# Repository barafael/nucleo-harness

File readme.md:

# Nucleo Harness

This circuit board is a harness for a nucleo board. It allows to embed a nucleo into a reproducible environment (less jumper wires).
2x16 pins can be connected to a saleae 16 protocol analyzer or any other 2x8 connector.
The mapping of pins which are connected to the 2x8 connectors can be made with jumper wires or with small addon PCBs.
Additionally, labeled pin header/sockets expose the regular nucleo64 pins.

TODO: duplicate programming connectors, allow for optional smd pullups

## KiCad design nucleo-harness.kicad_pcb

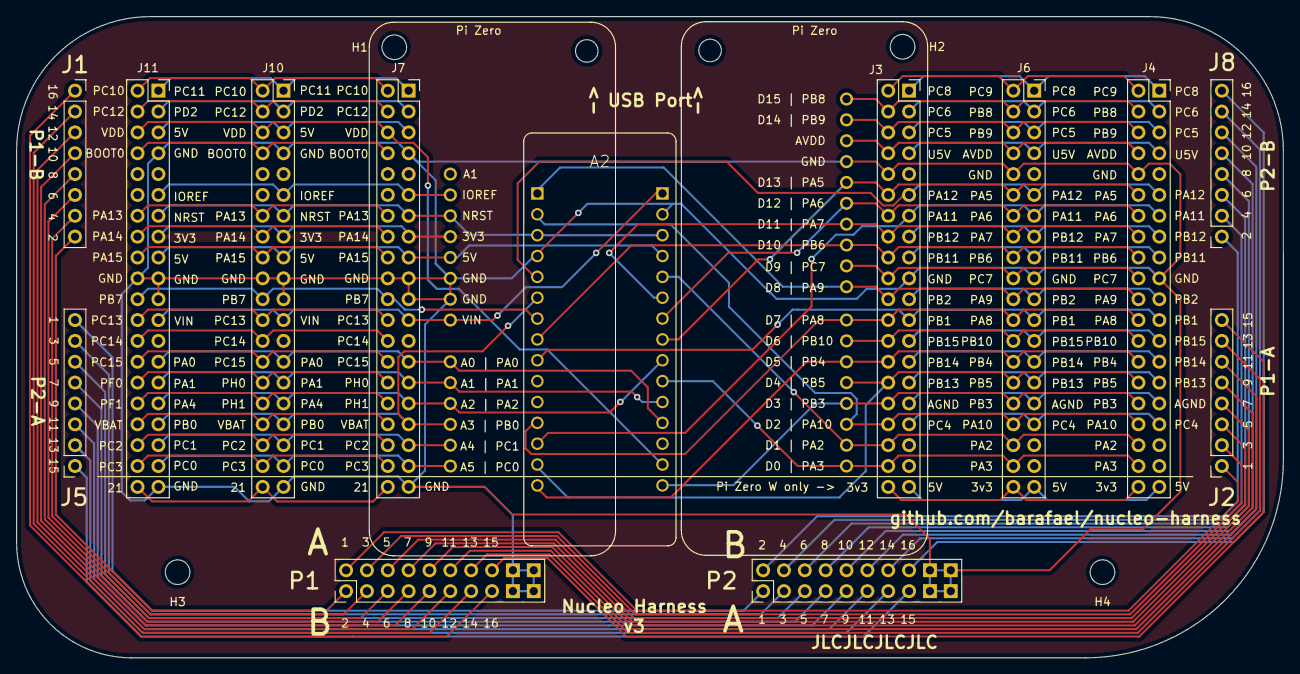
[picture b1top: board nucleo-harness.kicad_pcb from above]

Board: 2 copper layers, 154.3 x 78.1 mm, 18 parts (1 on the bottom side), 99 nets.

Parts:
A1: Arduino_UNO_R3
A2: NUCLEO-32; MODULE_NUCLEO-F303K8
H1, H2, H3, H4: MountingHole; MountingHole_3mm
J1, J2, J5, J8: Conn_01x08_Female; PinSocket_1x08_P2.54mm_Vertical
J3, J4, J6, J7, J10, J11: Conn_02x20_Odd_Even; PinSocket_2x20_P2.54mm_Vertical
P1, P2: Conn_02x10_Odd_Even; PinHeader_2x10_P2.54mm_Vertical

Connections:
3V3: A1.4, J7.15, J10.15, J11.15
5V: A1.5, A2.4.4, J7.17, J10.17, J11.17
AGND: J3.31, J4.31, J6.31
AVDD: A1.30, J3.8, J4.8, J6.8
BOOT0: J7.8, J10.8, J11.8
E5V: J7.5, J10.5, J11.5
GND: A1.6, A1.7, A1.29, A2.3.4, A2.4.2, J3.10, J3.19, J4.10, J4.19, J6.10, J6.19, J7.7, J7.19, J7.20, J7.21, J7.39, J10.7, J10.19, J10.20, J10.21, J10.39, J11.7, J11.19, J11.20, J11.21, J11.39, P1.17, P1.18, P1.19, P1.20, P2.17, P2.18, P2.19, P2.20
GPIO21: J7.40, J10.40, J11.40
IOREF: A1.2, J7.11, J10.11, J11.11
NRST: A1.3, A2.3.3, A2.4.3, J7.13, J10.13, J11.13
unnamed: J1.1, P1.15
unnamed: J1.2, P1.13
unnamed: J1.3, P1.11
unnamed: J1.4, P1.9
unnamed: J1.5, P1.7
unnamed: J1.6, P1.5
unnamed: J1.7, P1.3
unnamed: J1.8, P1.1
unnamed: J2.1, P1.2
unnamed: J2.2, P1.4
unnamed: J2.3, P1.6
unnamed: J2.4, P1.8
unnamed: J2.5, P1.10
unnamed: J2.6, P1.12
unnamed: J2.7, P1.14
unnamed: J2.8, P1.16
unnamed: J5.1, P2.15
unnamed: J5.2, P2.13
unnamed: J5.3, P2.11
unnamed: J5.4, P2.9
unnamed: J5.5, P2.7
unnamed: J5.6, P2.5
unnamed: J5.7, P2.3
unnamed: J5.8, P2.1
unnamed: J8.1, P2.2
unnamed: J8.2, P2.4
unnamed: J8.3, P2.6
unnamed: J8.4, P2.8
unnamed: J8.5, P2.10
unnamed: J8.6, P2.12
unnamed: J8.7, P2.14
unnamed: J8.8, P2.16
PA0: A1.9, A2.4.12, J7.27, J10.27, J11.27
PA1: A1.10, A2.4.11, J7.29, J10.29, J11.29
PA2: A1.16, A2.4.5, J3.36, J4.36, J6.36
PA3: A1.15, A2.4.10, J3.38, J4.38, J6.38
PA4: A1.11, A2.4.9, J7.31, J10.31, J11.31
PA5: A1.28, A2.4.8, J3.12, J4.12, J6.12
PA6: A1.27, A2.4.7, J3.14, J4.14, J6.14
PA7: A1.26, A2.4.6, J3.16, J4.16, J6.16
PA8: A1.22, A2.3.12, J3.24, J4.24, J6.24
PA9: A1.23, A2.3.1, J3.22, J4.22, J6.22
PA10: A1.17, A2.3.2, J3.34, J4.34, J6.34
PA11: A2.3.13, J3.13, J4.13, J6.13
PA12: A2.3.5, J3.11, J4.11, J6.11
PA13: J7.14, J10.14, J11.14
PA14: J7.16, J10.16, J11.16
PA15: J7.18, J10.18, J11.18
PB0: A1.12, A2.3.6, J7.33, J10.33, J11.33
PB1: A2.3.9, J3.23, J4.23, J6.23
PB2: J3.21, J4.21, J6.21
PB3: A1.18, A2.4.15, J3.32, J4.32, J6.32
PB4: A1.20, A2.3.15, J3.28, J4.28, J6.28
PB5: A1.19, A2.3.14, J3.30, J4.30, J6.30
PB6: A1.25, A2.3.8, J3.18, J4.18, J6.18
PB7: A2.3.7, J7.22, J10.22, J11.22
PB8: A1.32, J3.4, J4.4, J6.4
PB9: A1.31, J3.6, J4.6, J6.6
PB10: A1.21, J3.26, J4.26, J6.26
PB11: J3.17, J4.17, J6.17
PB12: J3.15, J4.15, J6.15
PB13: J3.29, J4.29, J6.29
PB14: J3.27, J4.27, J6.27
PB15: J3.25, J4.25, J6.25
PC0: A1.14, J7.37, J10.37, J11.37
PC1: A1.13, J7.35, J10.35, J11.35
PC2: J7.36, J10.36, J11.36
PC3: J7.38, J10.38, J11.38
PC4: J3.33, J4.33, J6.33
PC5: J3.5, J4.5, J6.5
PC6: J3.3, J4.3, J6.3
PC7: A1.24, J3.20, J4.20, J6.20
PC8: J3.1, J4.1, J6.1
PC9: J3.2, J4.2, J6.2
PC10: J7.2, J10.2, J11.2
PC11: J7.1, J10.1, J11.1
PC12: J7.4, J10.4, J11.4
PC13: J7.24, J10.24, J11.24
PC14: J7.26, J10.26, J11.26
PC15: J7.28, J10.28, J11.28
PD2: J7.3, J10.3, J11.3
PH0: J7.30, J10.30, J11.30
PH1: J7.32, J10.32, J11.32
POW_3v3: J3.40, J4.40, J6.40
POW_5V: J3.39, J4.39, J6.39
U5V: J3.7, J4.7, J6.7
VBAT: J7.34, J10.34, J11.34
VDD: A2.4.14, J7.6, J10.6, J11.6
VIN: A1.8, A2.4.1, J7.23, J10.23, J11.23

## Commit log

2019-11-03 add v1
2019-11-03 add readme
2019-11-03 add board render
2019-12-03 add pb11 label, change ph0/1 to pf0/1
2021-01-03 Add v2
2021-01-03 Add new board render
2021-01-03 Add mounting holes
2021-01-20 Add missing labels
2021-01-31 Add Pi Zero Footprint support
2021-01-31 Improve Pi Zero footprint
2021-02-27 Add nucleo32
2021-02-27 Update PCB with nucleo32 support
